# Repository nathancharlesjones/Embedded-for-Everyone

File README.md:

# Embedded for Everyone
A collection of resources for the hobbyists, students, teachers, and makers who want to develop professional-grade embedded systems but who lack the resources of a commercial enterprise.

See the [wiki for this repository](https://github.com/nathancharlesjones/Embedded-for-Everyone/wiki) for additional information and an explanation of the files contained herein.

## File structure
```
./
├── Getting-Started-Guides
│   ├── LPC845-BRK
│   │   ├── Command-line
│   │   │   ├── Blinky_v2
│   │   │   ├── Blinky_v3
│   │   │   ├── OpenOCD_and_CMSIS-DAP.sh
│   │   │   └── OpenOCD_and_J-Link.sh
│   │   ├── NXP-MCUXpresso
│   │   ├── Segger-Embedded-Studio
│   │   └── Getting-Started-with-the-LPC845-BRK.pdf
│   ├── MSP430
│   │   ├── CCStudio
│   │   ├── Getting-Started-with-the-MSP430.pdf
│   │   └── MSP430G2553.fzz
│   ├── PIC16-PIC18-dsPIC33
│   │   ├── dsPIC33
│   │   │   ├── Command-line
│   │   │   └── MPLAB-X
│   │   ├── PIC16
│   │   │   ├── Command-line
│   │   │   └── MPLAB-X
│   │   ├── dsPIC33EV32GM002.fzz
│   │   ├── Getting-Started-with-the-PIC16-PIC18-dsPIC33.pdf
│   │   └── PIC16F18446.fzz
│   ├── STM32G031J6
│   │   ├── Command-line
│   │   │   ├── libopencm3
│   │   │   ├── STM32Cube
│   │   │   ├── Start-ST-Link-GDB-Server.sh
│   │   │   └── Start-ST-Link-GDB-Server_v2.sh
│   │   ├── Keil-MDK-Arm
│   │   ├── STM32CubeIDE
│   │   └── Getting-Started-with-the-STM32G031J6.pdf
│   ├── XMC2GO_XMC1100
│   │   ├── Command-line
│   │   │   ├── Blinky
│   │   │   ├── Blinky_v2
│   │   │   └── OpenOCD_and_J-Link.sh
│   │   ├── DAVE
│   │   ├── Segger-Embedded-Studio
│   │   ├── VS-Code
│   │   └── Getting-Started-with-the-XMC2GO-XMC1100.pdf
│   ├── Compatible-Toolchains.csv
│   └── Compatible-Toolchains.ods
├── Printed-Circuit-Boards
│   ├── Breakout-boards
│   │   ├── STM32F030F4P6-Breakout-Boards
│   │   └── STM32G0-Breakout-Boards
│   ├── Eagle-Design-Rule-Files
│   └── Prototyping-PCBs
│       ├── Breadboard-Panelized
│       ├── Breadboard-Single
│       ├── Stripboard-Panelized
│       ├── Stripboard-Single
│       └── README.md
├── Supporting-documents
├── Embedded-for-Everyone.pdf
├── LICENSE
└── README.md
```

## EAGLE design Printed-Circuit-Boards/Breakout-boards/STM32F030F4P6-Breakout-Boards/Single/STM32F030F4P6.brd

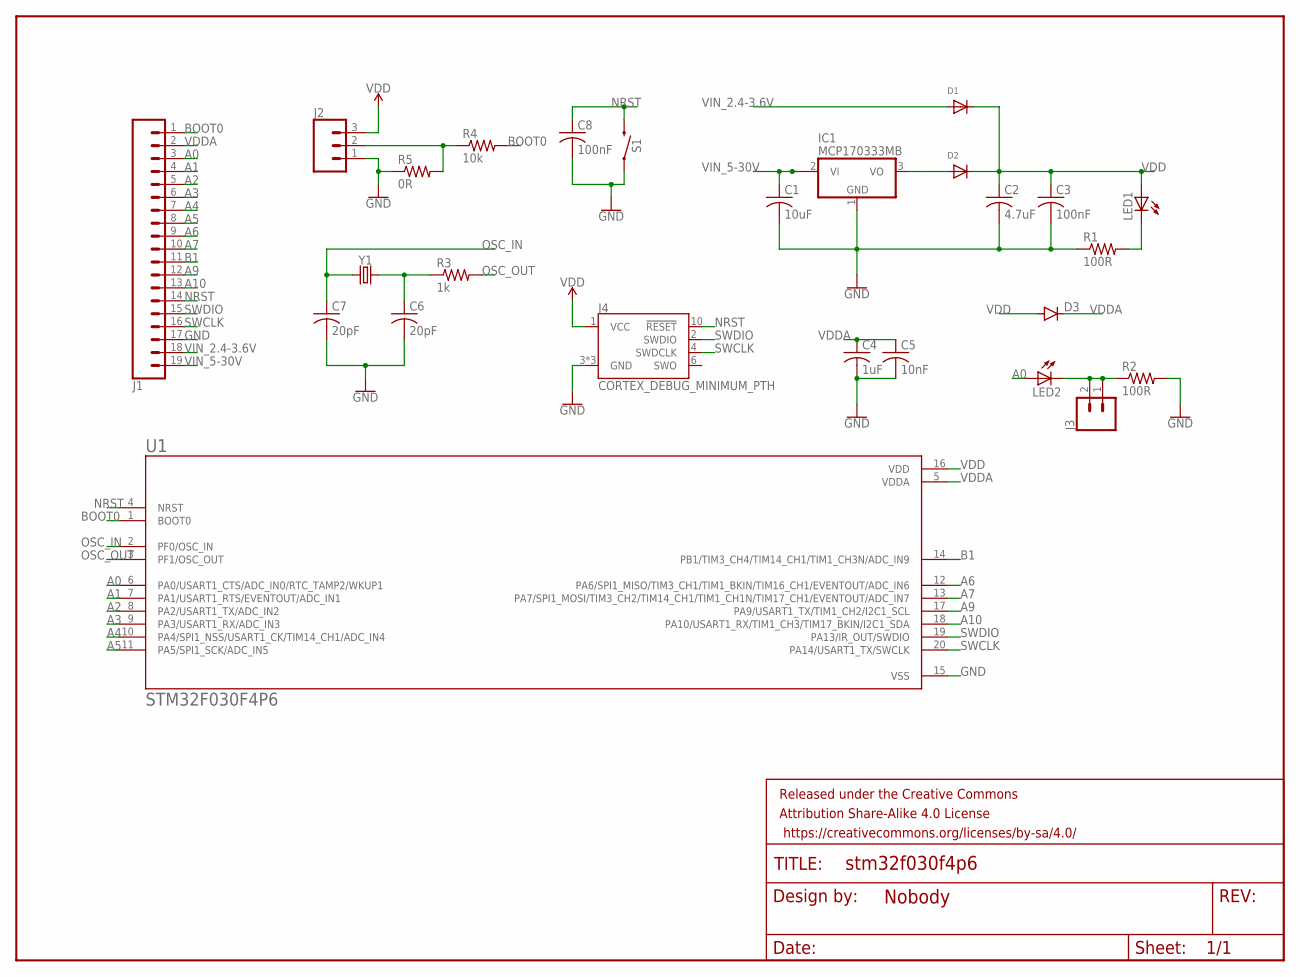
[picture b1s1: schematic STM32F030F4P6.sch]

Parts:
C1: 10uF; C0603
C2: 4.7uF; C0603
C3, C8: 100nF; C0603
C4: 1uF; C0603
C5: 10nF; C0603
C6, C7: 20pF; C0603
D1, D2: DIODESOD-123; SOD-123
D3: DIODE-DO-214AC; DO-214AC
FRAME2: FRAME-LETTERNO_PACKAGE; DUMMY
IC1: MCP170333MB; SOT89
J1: CONN_19; 1X19
J2: 455-1750-1-ND; 1X03
J3: CONN_02; 1X02
J4: CORTEX_DEBUG_MINIMUM_PTH; 2X5-PTH-1.27MM
LED1, LED2: LEDCHIPLED_0603; CHIPLED_0603
R1, R2: 100R; R0603
R3: 1k; R0603
R4: 10k; R0603
R5: 0R; R0603
S1: MOMENTARY-SWITCH-SPST-SMD-5.2-REDUNDANT; TACTILE_SWITCH_SMD_5.2MM
U1: STM32F030F4P6; SOP65P640X120-20N
Y1: CRYSTALSMD-5X3.2-2PAD; CRYSTAL-SMD-5X3.2-2PAD

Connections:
A0: J1.3, LED2.A, U1.6 (PA0/USART1_CTS/ADC_IN0/RTC_TAMP2/WKUP1)
A1: J1.4, U1.7 (PA1/USART1_RTS/EVENTOUT/ADC_IN1)
A2: J1.5, U1.8 (PA2/USART1_TX/ADC_IN2)
A3: J1.6, U1.9 (PA3/USART1_RX/ADC_IN3)
A4: J1.7, U1.10 (PA4/SPI1_NSS/USART1_CK/TIM14_CH1/ADC_IN4)
A5: J1.8, U1.11 (PA5/SPI1_SCK/ADC_IN5)
A6: J1.9, U1.12 (PA6/SPI1_MISO/TIM3_CH1/TIM1_BKIN/TIM16_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)
A7: J1.10, U1.13 (PA7/SPI1_MOSI/TIM3_CH2/TIM14_CH1/TIM1_C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)
A9: J1.12, U1.17 (PA9/USART1_TX/TIM1_CH2/I2C1_SCL)
A10: J1.13, U1.18 (PA10/USART1_RX/TIM1_CH3/TIM17_BKIN/I2C1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)
B1: J1.11, U1.14 (PB1/TIM3_CH4/TIM14_CH1/TIM1_CH3N/ADC_IN9)
BOOT0: J1.1, R4.2, U1.1 (BOOT0)
GND: C1.2, C2.2, C3.2, C4.2, C5.2, C6.2, C7.2, C8.2, IC1.1 (GND), J1.17, J2.1, J4.3 (GND), J4.5 (GND), J4.9 (GND), R1.1, R2.2, R5.1, S1.1, S1.2 (1), U1.15 (VSS)
unnamed: J2.2, R4.1, R5.2
unnamed: J3.1, J3.2, LED2.C, R2.1
unnamed: C6.1, R3.1, Y1.P$1 (1)
unnamed: D2.A, IC1.3 (VO)
unnamed: LED1.C, R1.2
NRST: C8.1, J1.14, J4.10 (!RESET), S1.3 (2), S1.4 (2), U1.4 (NRST)
OSC_IN: C7.1, U1.2 (PF0/OSC_IN), Y1.P$2 (2)
OSC_OUT: R3.2, U1.3 (PF1/OSC_OUT)
SWCLK: J1.16, J4.4 (SWDCLK), U1.20 (PA14/USART1_TX/SWCLK)
SWDIO: J1.15, J4.2 (SWDIO), U1.19 (PA13/IR_OUT/SWDIO)
VDD: C2.1, C3.1, D1.C, D2.C, D3.A, J2.3, J4.1 (VCC), LED1.A, U1.16 (VDD)
VDDA: C4.1, C5.1, D3.C, J1.2, U1.5 (VDDA)
VIN_2.4-3.6V: D1.A, J1.18
VIN_5-30V: C1.1, IC1.2@1 (VI1), J1.19

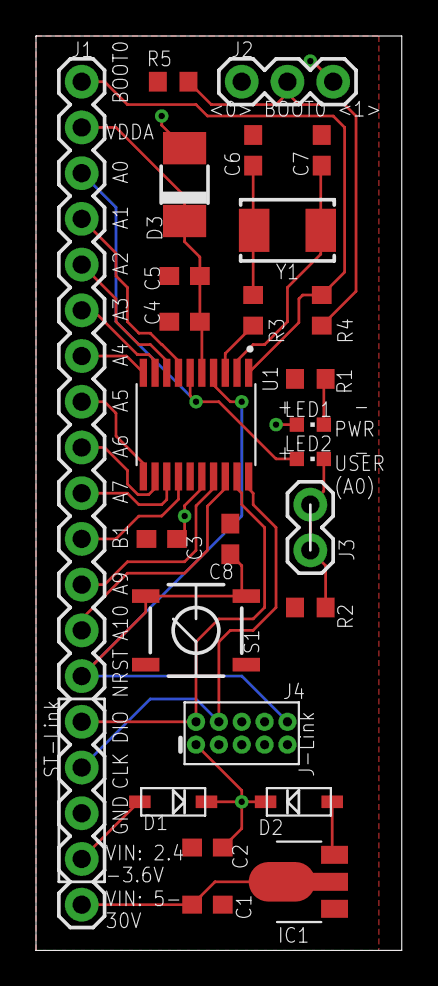
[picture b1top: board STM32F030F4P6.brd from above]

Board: 2 copper layers, 20.3 x 50.8 mm, 27 parts (0 on the bottom side), 27 nets.

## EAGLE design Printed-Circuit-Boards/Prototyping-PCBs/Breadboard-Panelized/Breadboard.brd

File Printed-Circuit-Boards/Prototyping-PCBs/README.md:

For information about the differences between stripboard and breadboard-style protoboard, see [here](https://github.com/nathancharlesjones/Embedded-for-Everyone/wiki/3.-Building-a-circuit-on-a-PCB-and-connecting-it-to-the-rest-of-the-embedded-device#step-3-lay-out-the-pcb-or-get-a-protoboard).

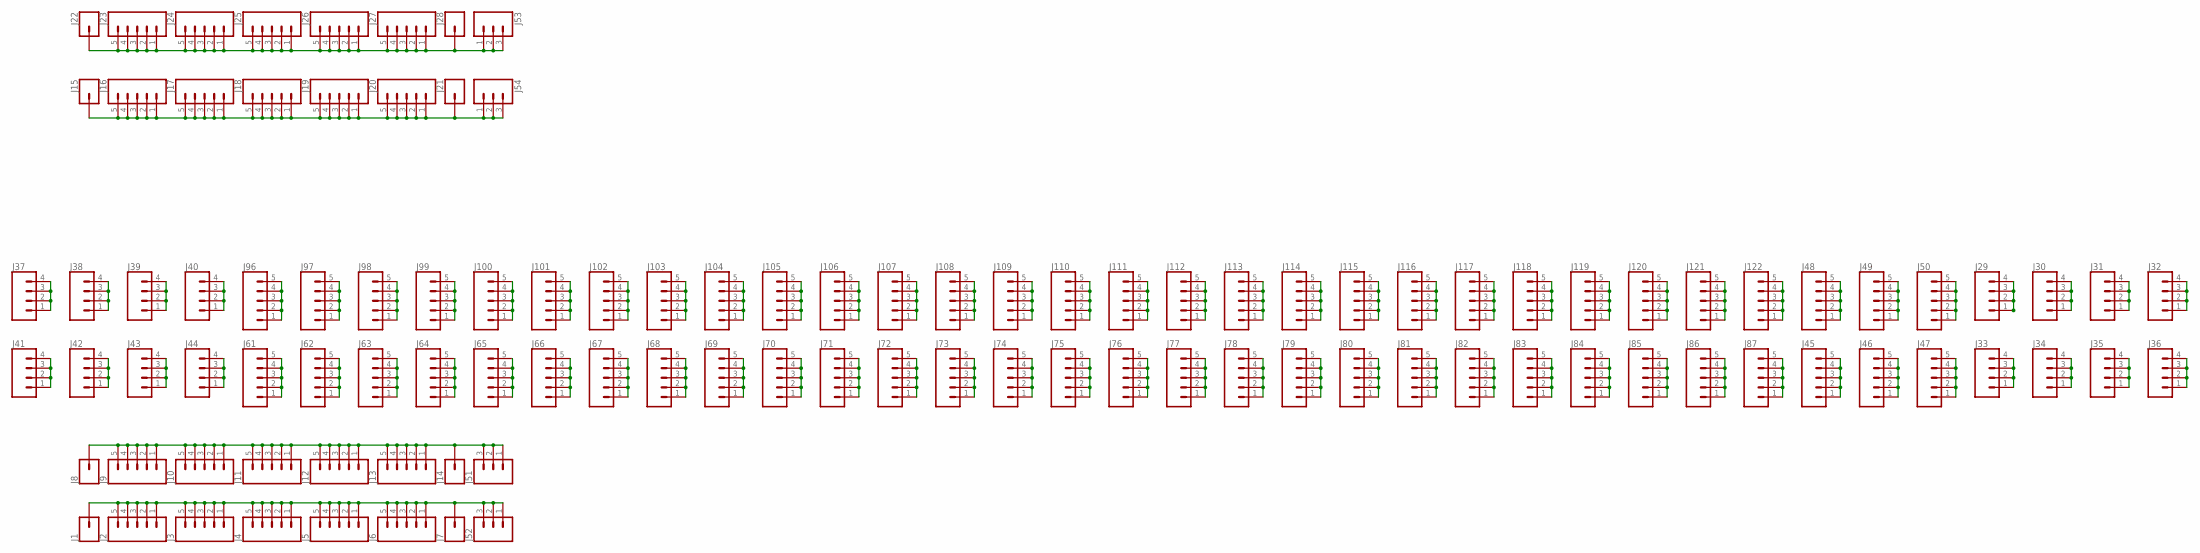
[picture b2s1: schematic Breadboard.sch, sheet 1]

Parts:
J1, J7, J8, J14, J15, J21, J22, J28: CONN_01; 1X01
J2, J3, J4, J5, J6, J9, J10, J11, J12, J13, J16, J17, J18, J19, J20, J23, J24, J25, J26, J27, J45, J46, J47, J48, J49, J50, J61, J62, J63, J64, J65, J66, J67, J68, J69, J70, J71, J72, J73, J74, J75, J76, J77, J78, J79, J80, J81, J82, J83, J84, J85, J86, J87, J96, J97, J98, J99, J100, J101, J102, J103, J104, J105, J106, J107, J108, J109, J110, J111, J112, J113, J114, J115, J116, J117, J118, J119, J120, J121, J122: CONN_05; 1X05
J29, J30, J31, J32, J33, J34, J35, J36, J37, J38, J39, J40, J41, J42, J43, J44: CONN_04PTH; 1X04
J51, J52, J53, J54: 455-1750-1-ND; 1X03

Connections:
unnamed: J1.1, J2.1, J2.2, J2.3, J2.4, J2.5, J3.1, J3.2, J3.3, J3.4, J3.5, J4.1, J4.2, J4.3, J4.4, J4.5, J5.1, J5.2, J5.3, J5.4, J5.5, J6.1, J6.2, J6.3, J6.4, J6.5, J7.1, J52.1, J52.2, J52.3
unnamed: J8.1, J9.1, J9.2, J9.3, J9.4, J9.5, J10.1, J10.2, J10.3, J10.4, J10.5, J11.1, J11.2, J11.3, J11.4, J11.5, J12.1, J12.2, J12.3, J12.4, J12.5, J13.1, J13.2, J13.3, J13.4, J13.5, J14.1, J51.1, J51.2, J51.3
unnamed: J15.1, J16.1, J16.2, J16.3, J16.4, J16.5, J17.1, J17.2, J17.3, J17.4, J17.5, J18.1, J18.2, J18.3, J18.4, J18.5, J19.1, J19.2, J19.3, J19.4, J19.5, J20.1, J20.2, J20.3, J20.4, J20.5, J21.1, J54.1, J54.2, J54.3
unnamed: J22.1, J23.1, J23.2, J23.3, J23.4, J23.5, J24.1, J24.2, J24.3, J24.4, J24.5, J25.1, J25.2, J25.3, J25.4, J25.5, J26.1, J26.2, J26.3, J26.4, J26.5, J27.1, J27.2, J27.3, J27.4, J27.5, J28.1, J53.1, J53.2, J53.3
unnamed: J41.1, J41.2, J41.3, J41.4
unnamed: J42.1, J42.2, J42.3, J42.4
unnamed: J43.1, J43.2, J43.3, J43.4
unnamed: J44.1, J44.2, J44.3, J44.4
unnamed: J61.1, J61.2, J61.3, J61.4, J61.5
unnamed: J62.1, J62.2, J62.3, J62.4, J62.5
unnamed: J63.1, J63.2, J63.3, J63.4, J63.5
unnamed: J64.1, J64.2, J64.3, J64.4, J64.5
unnamed: J65.1, J65.2, J65.3, J65.4, J65.5
unnamed: J66.1, J66.2, J66.3, J66.4, J66.5
unnamed: J67.1, J67.2, J67.3, J67.4, J67.5
unnamed: J68.1, J68.2, J68.3, J68.4, J68.5
unnamed: J69.1, J69.2, J69.3, J69.4, J69.5
unnamed: J70.1, J70.2, J70.3, J70.4, J70.5
unnamed: J71.1, J71.2, J71.3, J71.4, J71.5
unnamed: J72.1, J72.2, J72.3, J72.4, J72.5
unnamed: J73.1, J73.2, J73.3, J73.4, J73.5
unnamed: J74.1, J74.2, J74.3, J74.4, J74.5
unnamed: J75.1, J75.2, J75.3, J75.4, J75.5
unnamed: J76.1, J76.2, J76.3, J76.4, J76.5
unnamed: J77.1, J77.2, J77.3, J77.4, J77.5
unnamed: J78.1, J78.2, J78.3, J78.4, J78.5
unnamed: J79.1, J79.2, J79.3, J79.4, J79.5
unnamed: J80.1, J80.2, J80.3, J80.4, J80.5
unnamed: J81.1, J81.2, J81.3, J81.4, J81.5
unnamed: J82.1, J82.2, J82.3, J82.4, J82.5
unnamed: J83.1, J83.2, J83.3, J83.4, J83.5
unnamed: J84.1, J84.2, J84.3, J84.4, J84.5
unnamed: J85.1, J85.2, J85.3, J85.4, J85.5
unnamed: J86.1, J86.2, J86.3, J86.4, J86.5
unnamed: J87.1, J87.2, J87.3, J87.4, J87.5
unnamed: J33.1, J33.2, J33.3, J33.4
unnamed: J34.1, J34.2, J34.3, J34.4
unnamed: J35.1, J35.2, J35.3, J35.4
unnamed: J36.1, J36.2, J36.3, J36.4
unnamed: J37.1, J37.2, J37.3, J37.4
unnamed: J38.1, J38.2, J38.3, J38.4
unnamed: J39.1, J39.2, J39.3, J39.4
unnamed: J40.1, J40.2, J40.3, J40.4
unnamed: J96.1, J96.2, J96.3, J96.4, J96.5
unnamed: J97.1, J97.2, J97.3, J97.4, J97.5
unnamed: J98.1, J98.2, J98.3, J98.4, J98.5
unnamed: J99.1, J99.2, J99.3, J99.4, J99.5
unnamed: J100.1, J100.2, J100.3, J100.4, J100.5
unnamed: J101.1, J101.2, J101.3, J101.4, J101.5
unnamed: J102.1, J102.2, J102.3, J102.4, J102.5
unnamed: J103.1, J103.2, J103.3, J103.4, J103.5
unnamed: J104.1, J104.2, J104.3, J104.4, J104.5
unnamed: J105.1, J105.2, J105.3, J105.4, J105.5
unnamed: J106.1, J106.2, J106.3, J106.4, J106.5
unnamed: J107.1, J107.2, J107.3, J107.4, J107.5
unnamed: J108.1, J108.2, J108.3, J108.4, J108.5
unnamed: J109.1, J109.2, J109.3, J109.4, J109.5
unnamed: J110.1, J110.2, J110.3, J110.4, J110.5
unnamed: J111.1, J111.2, J111.3, J111.4, J111.5
unnamed: J112.1, J112.2, J112.3, J112.4, J112.5
unnamed: J113.1, J113.2, J113.3, J113.4, J113.5
unnamed: J114.1, J114.2, J114.3, J114.4, J114.5
unnamed: J115.1, J115.2, J115.3, J115.4, J115.5
unnamed: J116.1, J116.2, J116.3, J116.4, J116.5
unnamed: J117.1, J117.2, J117.3, J117.4, J117.5
unnamed: J118.1, J118.2, J118.3, J118.4, J118.5
unnamed: J119.1, J119.2, J119.3, J119.4, J119.5
unnamed: J120.1, J120.2, J120.3, J120.4, J120.5
unnamed: J121.1, J121.2, J121.3, J121.4, J121.5
unnamed: J122.1, J122.2, J122.3, J122.4, J122.5
unnamed: J29.1, J29.2, J29.3, J29.4
unnamed: J30.1, J30.2, J30.3, J30.4
unnamed: J31.1, J31.2, J31.3, J31.4
unnamed: J32.1, J32.2, J32.3, J32.4
unnamed: J48.1, J48.2, J48.3, J48.4, J48.5
unnamed: J45.1, J45.2, J45.3, J45.4, J45.5
unnamed: J46.1, J46.2, J46.3, J46.4, J46.5
unnamed: J47.1, J47.2, J47.3, J47.4, J47.5
unnamed: J49.1, J49.2, J49.3, J49.4, J49.5
unnamed: J50.1, J50.2, J50.3, J50.4, J50.5

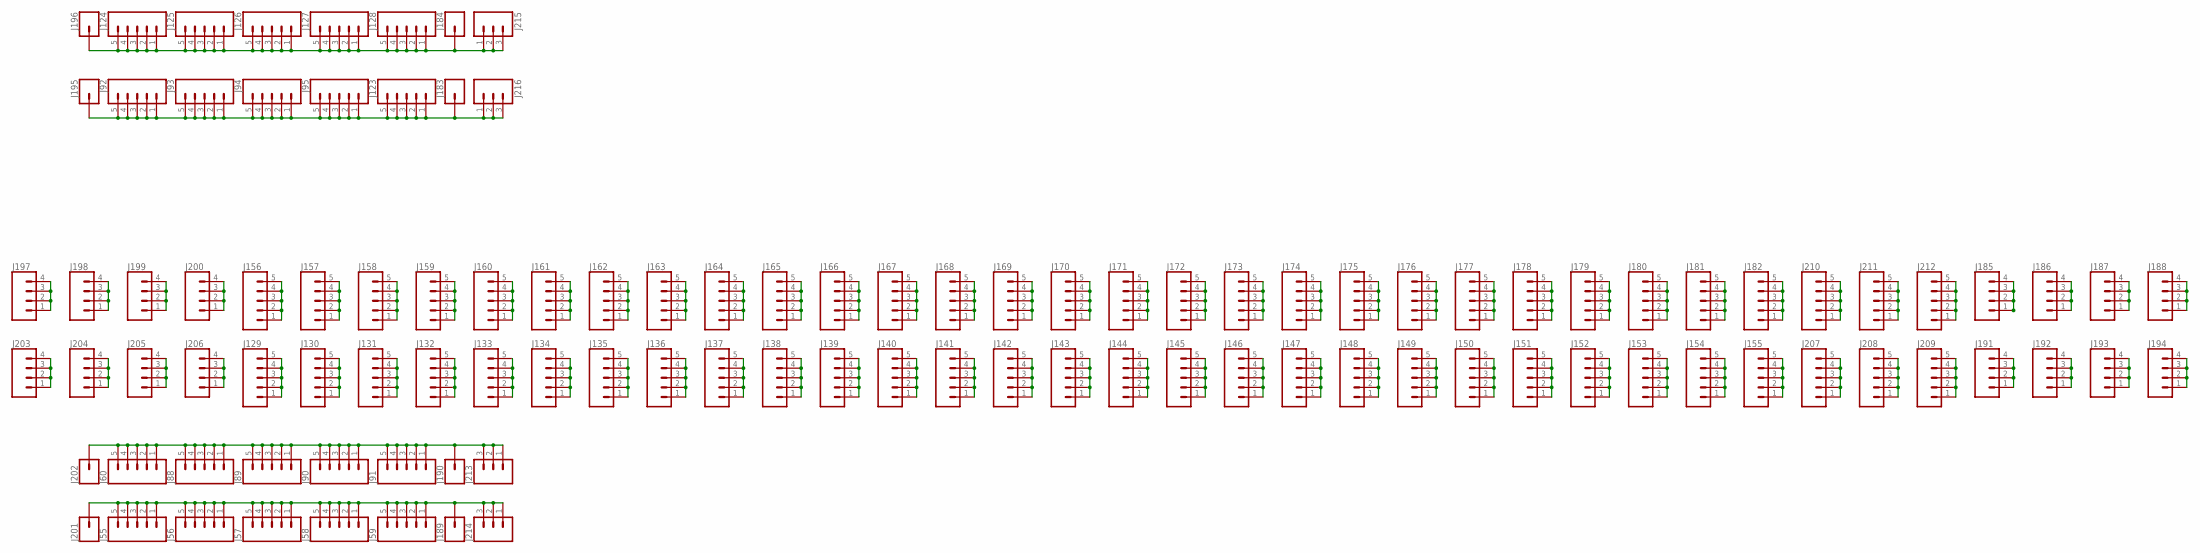
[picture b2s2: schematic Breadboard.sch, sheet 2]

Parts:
J55, J56, J57, J58, J59, J60, J88, J89, J90, J91, J92, J93, J94, J95, J123, J124, J125, J126, J127, J128, J129, J130, J131, J132, J133, J134, J135, J136, J137, J138, J139, J140, J141, J142, J143, J144, J145, J146, J147, J148, J149, J150, J151, J152, J153, J154, J155, J156, J157, J158, J159, J160, J161, J162, J163, J164, J165, J166, J167, J168, J169, J170, J171, J172, J173, J174, J175, J176, J177, J178, J179, J180, J181, J182, J207, J208, J209, J210, J211, J212: CONN_05; 1X05
J183, J184, J189, J190, J195, J196, J201, J202: CONN_01; 1X01
J185, J186, J187, J188, J191, J192, J193, J194, J197, J198, J199, J200, J203, J204, J205, J206: CONN_04PTH; 1X04
J213, J214, J215, J216: 455-1750-1-ND; 1X03

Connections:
unnamed: J55.1, J55.2, J55.3, J55.4, J55.5, J56.1, J56.2, J56.3, J56.4, J56.5, J57.1, J57.2, J57.3, J57.4, J57.5, J58.1, J58.2, J58.3, J58.4, J58.5, J59.1, J59.2, J59.3, J59.4, J59.5, J189.1, J201.1, J214.1, J214.2, J214.3
unnamed: J60.1, J60.2, J60.3, J60.4, J60.5, J88.1, J88.2, J88.3, J88.4, J88.5, J89.1, J89.2, J89.3, J89.4, J89.5, J90.1, J90.2, J90.3, J90.4, J90.5, J91.1, J91.2, J91.3, J91.4, J91.5, J190.1, J202.1, J213.1, J213.2, J213.3
unnamed: J92.1, J92.2, J92.3, J92.4, J92.5, J93.1, J93.2, J93.3, J93.4, J93.5, J94.1, J94.2, J94.3, J94.4, J94.5, J95.1, J95.2, J95.3, J95.4, J95.5, J123.1, J123.2, J123.3, J123.4, J123.5, J183.1, J195.1, J216.1, J216.2, J216.3
unnamed: J124.1, J124.2, J124.3, J124.4, J124.5, J125.1, J125.2, J125.3, J125.4, J125.5, J126.1, J126.2, J126.3, J126.4, J126.5, J127.1, J127.2, J127.3, J127.4, J127.5, J128.1, J128.2, J128.3, J128.4, J128.5, J184.1, J196.1, J215.1, J215.2, J215.3
unnamed: J203.1, J203.2, J203.3, J203.4
unnamed: J204.1, J204.2, J204.3, J204.4
unnamed: J205.1, J205.2, J205.3, J205.4
unnamed: J206.1, J206.2, J206.3, J206.4
unnamed: J129.1, J129.2, J129.3, J129.4, J129.5
unnamed: J130.1, J130.2, J130.3, J130.4, J130.5
unnamed: J131.1, J131.2, J131.3, J131.4, J131.5
unnamed: J132.1, J132.2, J132.3, J132.4, J132.5
unnamed: J133.1, J133.2, J133.3, J133.4, J133.5
unnamed: J134.1, J134.2, J134.3, J134.4, J134.5
unnamed: J135.1, J135.2, J135.3, J135.4, J135.5
unnamed: J136.1, J136.2, J136.3, J136.4, J136.5
unnamed: J137.1, J137.2, J137.3, J137.4, J137.5
unnamed: J138.1, J138.2, J138.3, J138.4, J138.5
unnamed: J139.1, J139.2, J139.3, J139.4, J139.5
unnamed: J140.1, J140.2, J140.3, J140.4, J140.5
unnamed: J141.1, J141.2, J141.3, J141.4, J141.5
unnamed: J142.1, J142.2, J142.3, J142.4, J142.5
unnamed: J143.1, J143.2, J143.3, J143.4, J143.5
unnamed: J144.1, J144.2, J144.3, J144.4, J144.5
unnamed: J145.1, J145.2, J145.3, J145.4, J145.5
unnamed: J146.1, J146.2, J146.3, J146.4, J146.5
unnamed: J147.1, J147.2, J147.3, J147.4, J147.5
unnamed: J148.1, J148.2, J148.3, J148.4, J148.5
unnamed: J149.1, J149.2, J149.3, J149.4, J149.5
unnamed: J150.1, J150.2, J150.3, J150.4, J150.5
unnamed: J151.1, J151.2, J151.3, J151.4, J151.5
unnamed: J152.1, J152.2, J152.3, J152.4, J152.5
unnamed: J153.1, J153.2, J153.3, J153.4, J153.5
unnamed: J154.1, J154.2, J154.3, J154.4, J154.5
unnamed: J155.1, J155.2, J155.3, J155.4, J155.5
unnamed: J191.1, J191.2, J191.3, J191.4
unnamed: J192.1, J192.2, J192.3, J192.4
unnamed: J193.1, J193.2, J193.3, J193.4
unnamed: J194.1, J194.2, J194.3, J194.4
unnamed: J197.1, J197.2, J197.3, J197.4
unnamed: J198.1, J198.2, J198.3, J198.4
unnamed: J199.1, J199.2, J199.3, J199.4
unnamed: J200.1, J200.2, J200.3, J200.4
unnamed: J156.1, J156.2, J156.3, J156.4, J156.5
unnamed: J157.1, J157.2, J157.3, J157.4, J157.5
unnamed: J158.1, J158.2, J158.3, J158.4, J158.5
unnamed: J159.1, J159.2, J159.3, J159.4, J159.5
unnamed: J160.1, J160.2, J160.3, J160.4, J160.5
unnamed: J161.1, J161.2, J161.3, J161.4, J161.5
unnamed: J162.1, J162.2, J162.3, J162.4, J162.5
unnamed: J163.1, J163.2, J163.3, J163.4, J163.5
unnamed: J164.1, J164.2, J164.3, J164.4, J164.5
unnamed: J165.1, J165.2, J165.3, J165.4, J165.5
unnamed: J166.1, J166.2, J166.3, J166.4, J166.5
unnamed: J167.1, J167.2, J167.3, J167.4, J167.5
unnamed: J168.1, J168.2, J168.3, J168.4, J168.5
unnamed: J169.1, J169.2, J169.3, J169.4, J169.5
unnamed: J170.1, J170.2, J170.3, J170.4, J170.5
unnamed: J171.1, J171.2, J171.3, J171.4, J171.5
unnamed: J172.1, J172.2, J172.3, J172.4, J172.5
unnamed: J173.1, J173.2, J173.3, J173.4, J173.5
unnamed: J174.1, J174.2, J174.3, J174.4, J174.5
unnamed: J175.1, J175.2, J175.3, J175.4, J175.5
unnamed: J176.1, J176.2, J176.3, J176.4, J176.5
unnamed: J177.1, J177.2, J177.3, J177.4, J177.5
unnamed: J178.1, J178.2, J178.3, J178.4, J178.5
unnamed: J179.1, J179.2, J179.3, J179.4, J179.5
unnamed: J180.1, J180.2, J180.3, J180.4, J180.5
unnamed: J181.1, J181.2, J181.3, J181.4, J181.5
unnamed: J182.1, J182.2, J182.3, J182.4, J182.5
unnamed: J185.1, J185.2, J185.3, J185.4
unnamed: J186.1, J186.2, J186.3, J186.4
unnamed: J187.1, J187.2, J187.3, J187.4
unnamed: J188.1, J188.2, J188.3, J188.4
unnamed: J207.1, J207.2, J207.3, J207.4, J207.5
unnamed: J208.1, J208.2, J208.3, J208.4, J208.5
unnamed: J209.1, J209.2, J209.3, J209.4, J209.5
unnamed: J210.1, J210.2, J210.3, J210.4, J210.5
unnamed: J211.1, J211.2, J211.3, J211.4, J211.5
unnamed: J212.1, J212.2, J212.3, J212.4, J212.5

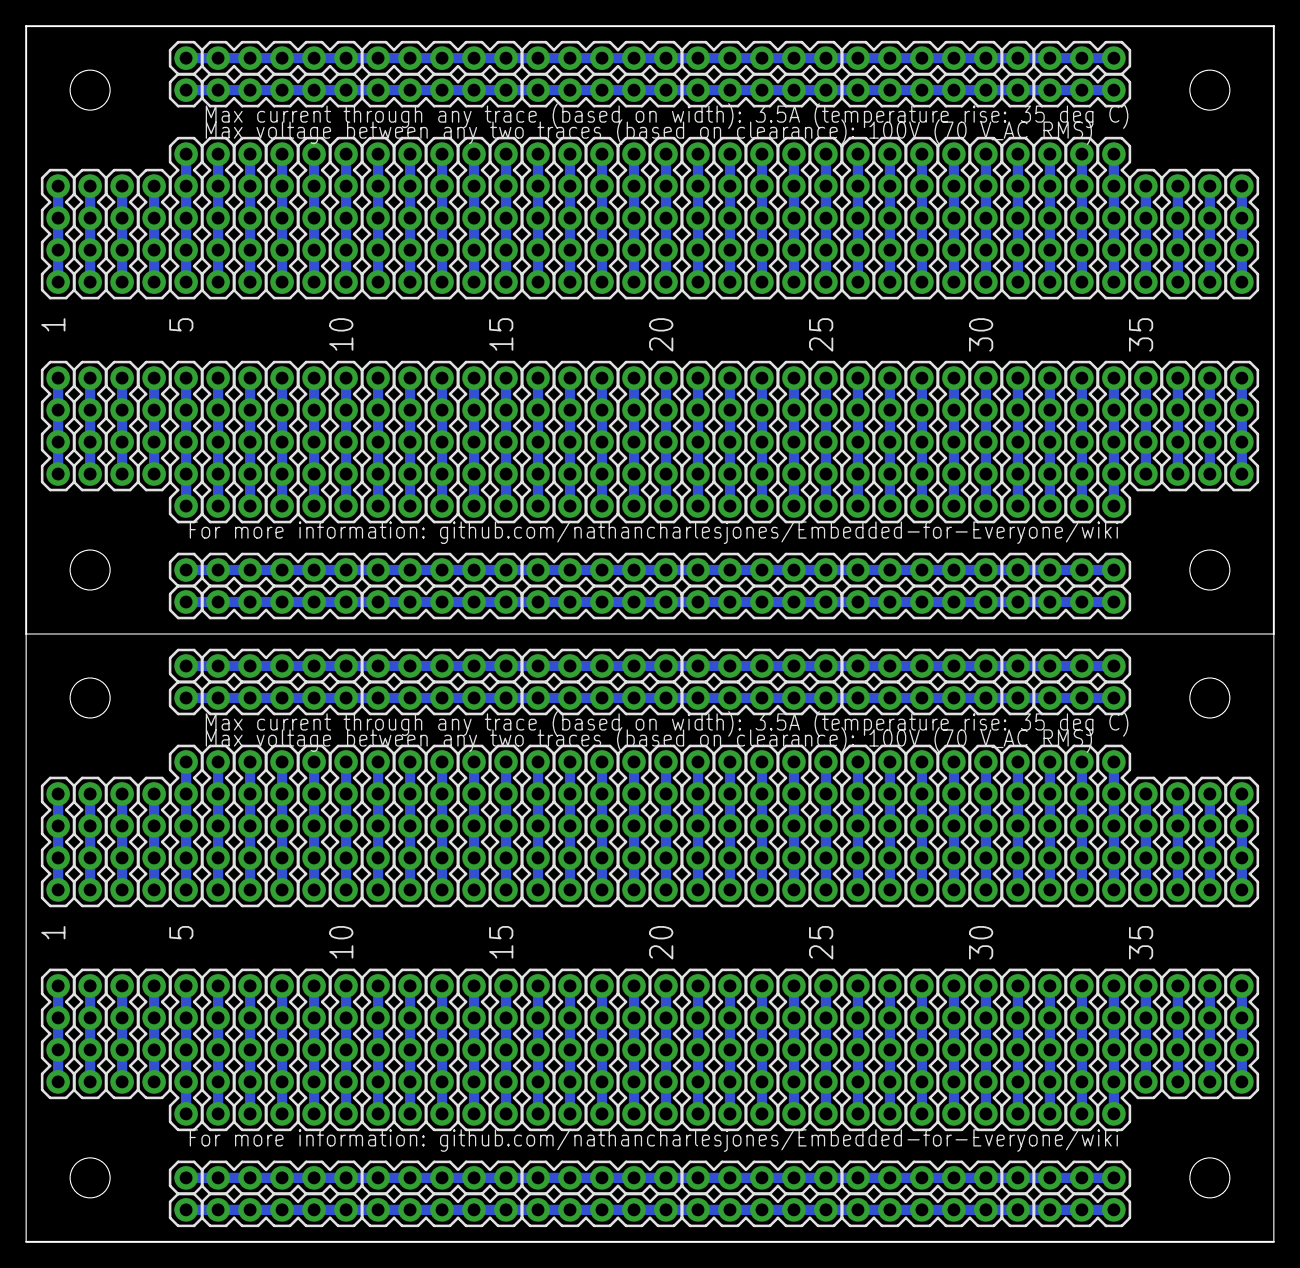
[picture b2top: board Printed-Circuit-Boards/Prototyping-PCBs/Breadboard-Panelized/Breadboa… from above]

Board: 2 copper layers, 99.1 x 96.5 mm, 216 parts (0 on the bottom side), 160 nets.

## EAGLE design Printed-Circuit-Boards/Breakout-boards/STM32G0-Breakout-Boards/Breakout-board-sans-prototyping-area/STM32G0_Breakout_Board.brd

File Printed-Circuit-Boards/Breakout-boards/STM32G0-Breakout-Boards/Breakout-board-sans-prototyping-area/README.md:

For information about how to order this PCB (either unassembled for full assembled), see [here](https://github.com/nathancharlesjones/Embedded-for-Everyone/wiki/3.-Building-a-circuit-on-a-PCB-and-connecting-it-to-the-rest-of-the-embedded-device#step-5-assemble-the-pcb).

This board was also designed with large-enough dimensions to be manufactured by hand using a PCB mill or other manual technique. If the method you use doesn't through-plate the vias, don't forget to connect them each yourself.

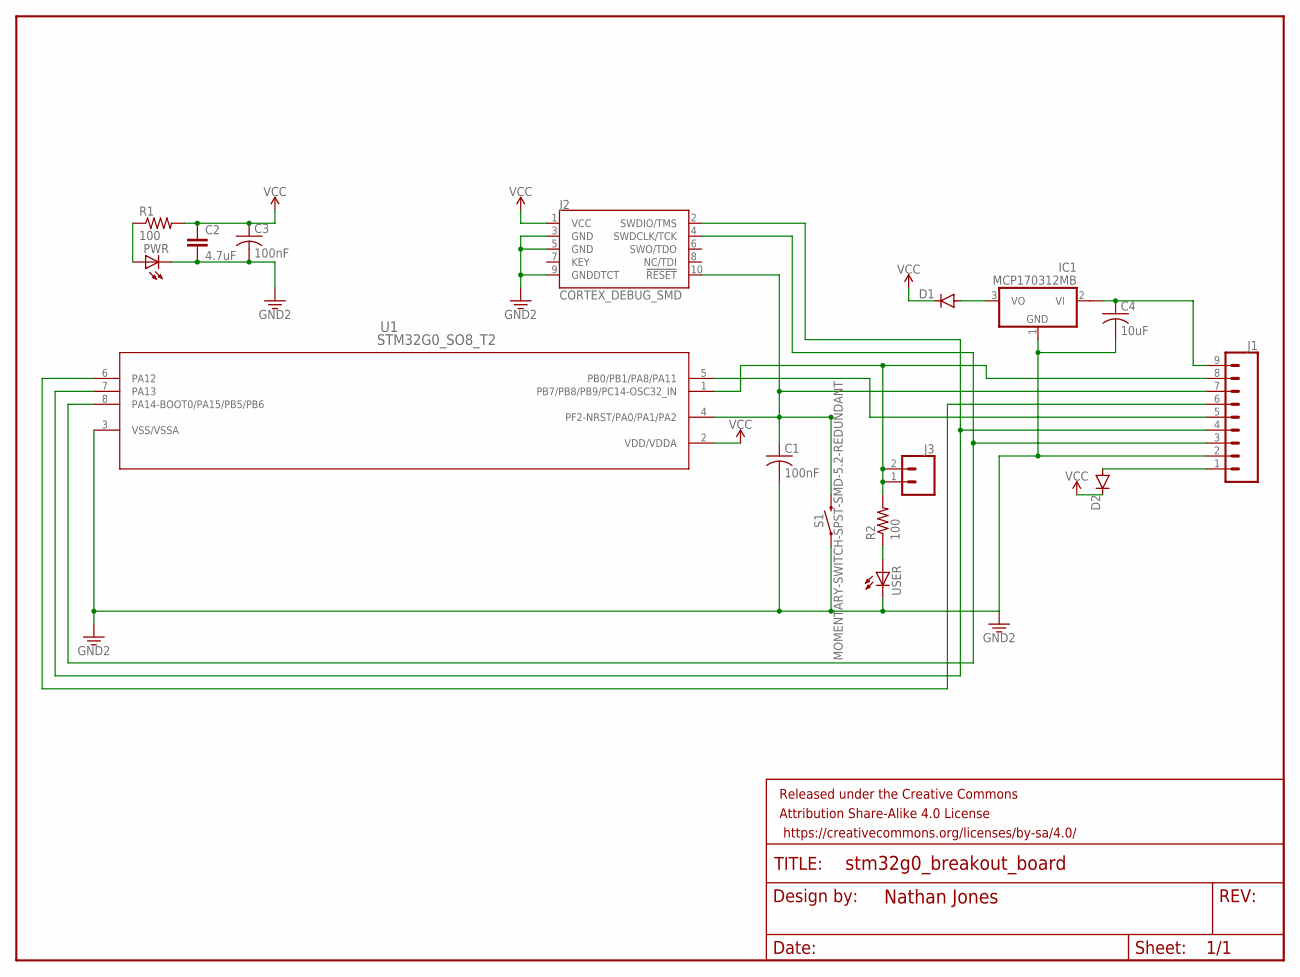
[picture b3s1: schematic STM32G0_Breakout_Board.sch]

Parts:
C1, C3: 100nF; C1206
C2: 4.7uF; 1206
C4: 10uF; C1206
D1, D2: DIODE-DO-214AC; DO-214AC
FRAME1: FRAME-LETTERNO_PACKAGE; DUMMY
IC1: MCP170312MB; SOT89
J1: CONN_09LONGPADS; 1X09_LONGPADS
J2: CORTEX_DEBUG_SMD; SAMTECH_FTSH-105-01
J3: CONN_02PTH3; 1X02_LONGPADS
PWR: LEDCHIP-LED0805; CHIP-LED0805
R1, R2: 100; R1206
S1: MOMENTARY-SWITCH-SPST-SMD-5.2-REDUNDANT; TACTILE_SWITCH_SMD_5.2MM
U1: STM32G0_SO8_T2; SO-8
USER: LEDCHIP-LED0805; CHIP-LED0805

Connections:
GND: C1.2, C2.2, C3.2, C4.2, IC1.1 (GND), J1.2, J2.3 (GND), J2.5 (GND), J2.9 (GNDDTCT), PWR.C, S1.1, S1.2 (1), U1.3 (VSS/VSSA), USER.C
unnamed: R2.1, USER.A
unnamed: D2.A, J1.1
unnamed: C4.1, IC1.2@1 (VI1), J1.9
unnamed: PWR.A, R1.1
unnamed: D1.A, IC1.3 (VO)
NRST/PA0/PA1/PA2: C1.1, J1.7, J2.10 (!RESET), S1.3 (2), S1.4 (2), U1.4 (PF2-NRST/PA0/PA1/PA2)
PA12: J1.6, U1.6 (PA12)
PB0/PB1/PA8/PA11: J1.5, U1.5 (PB0/PB1/PA8/PA11)
PC14: J1.8, J3.1, J3.2, R2.2, U1.1 (PB7/PB8/PB9/PC14-OSC32_IN)
SWDCLK: J1.3, J2.4 (SWDCLK/TCK), U1.8 (PA14-BOOT0/PA15/PB5/PB6)
SWDIO: J1.4, J2.2 (SWDIO/TMS), U1.7 (PA13)
VCC: C2.1, C3.1, D1.C, D2.C, J2.1 (VCC), R1.2, U1.2 (VDD/VDDA)

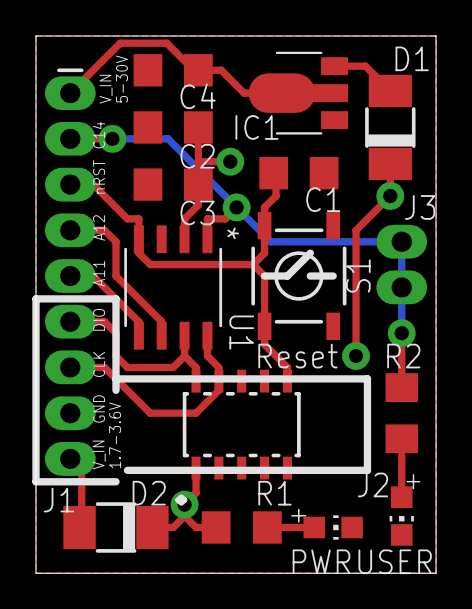
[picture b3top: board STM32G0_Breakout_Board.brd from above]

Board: 2 copper layers, 22.2 x 29.8 mm, 17 parts (0 on the bottom side), 13 nets.

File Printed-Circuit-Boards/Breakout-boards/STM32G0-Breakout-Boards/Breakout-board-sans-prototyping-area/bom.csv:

Comment,Designator,Footprint,LCSC Part #（optional）
100nF,"C1,C3",1206_C,C24497
4.7uF,C2,1206_C,C29823
10uF,C4,1206_C,C13585
,"D1,D2",DO-214AC,C2480
3.3V,IC1,SOT-89-3,C14289
,"PWR,USER",0805,C84256
100Ω,"R1, R2",1206_R,C17901
,S1,5.1mmx5.1mm,C318884
,U1,SOIC-8,C432201

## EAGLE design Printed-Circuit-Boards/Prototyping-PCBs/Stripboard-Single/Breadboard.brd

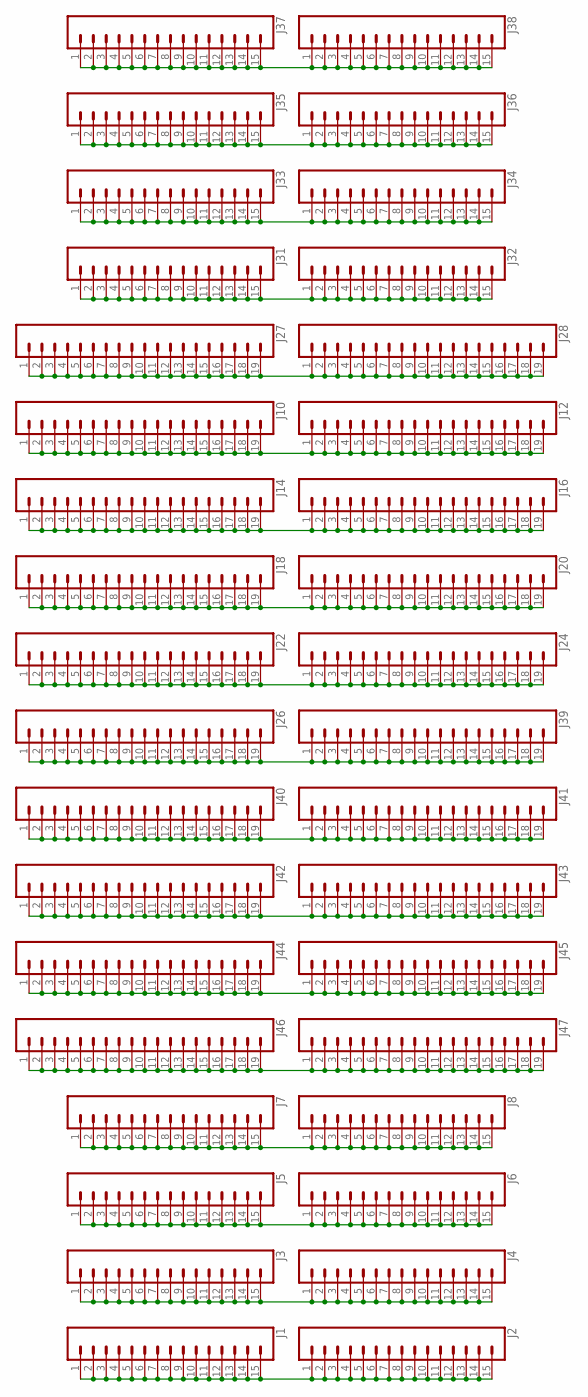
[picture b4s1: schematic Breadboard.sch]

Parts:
J1, J2, J3, J4, J5, J6, J7, J8, J31, J32, J33, J34, J35, J36, J37, J38: CONN_15; 1X15
J10, J12, J14, J16, J18, J20, J22, J24, J26, J27, J28, J39, J40, J41, J42, J43, J44, J45, J46, J47: CONN_19; 1X19

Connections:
unnamed: J37.1, J37.2, J37.3, J37.4, J37.5, J37.6, J37.7, J37.8, J37.9, J37.10, J37.11, J37.12, J37.13, J37.14, J37.15, J38.1, J38.2, J38.3, J38.4, J38.5, J38.6, J38.7, J38.8, J38.9, J38.10, J38.11, J38.12, J38.13, J38.14, J38.15
unnamed: J35.1, J35.2, J35.3, J35.4, J35.5, J35.6, J35.7, J35.8, J35.9, J35.10, J35.11, J35.12, J35.13, J35.14, J35.15, J36.1, J36.2, J36.3, J36.4, J36.5, J36.6, J36.7, J36.8, J36.9, J36.10, J36.11, J36.12, J36.13, J36.14, J36.15
unnamed: J33.1, J33.2, J33.3, J33.4, J33.5, J33.6, J33.7, J33.8, J33.9, J33.10, J33.11, J33.12, J33.13, J33.14, J33.15, J34.1, J34.2, J34.3, J34.4, J34.5, J34.6, J34.7, J34.8, J34.9, J34.10, J34.11, J34.12, J34.13, J34.14, J34.15
unnamed: J31.1, J31.2, J31.3, J31.4, J31.5, J31.6, J31.7, J31.8, J31.9, J31.10, J31.11, J31.12, J31.13, J31.14, J31.15, J32.1, J32.2, J32.3, J32.4, J32.5, J32.6, J32.7, J32.8, J32.9, J32.10, J32.11, J32.12, J32.13, J32.14, J32.15
unnamed: J27.1, J27.2, J27.3, J27.4, J27.5, J27.6, J27.7, J27.8, J27.9, J27.10, J27.11, J27.12, J27.13, J27.14, J27.15, J27.16, J27.17, J27.18, J27.19, J28.1, J28.2, J28.3, J28.4, J28.5, J28.6, J28.7, J28.8, J28.9, J28.10, J28.11, J28.12, J28.13, J28.14, J28.15, J28.16, J28.17, J28.18, J28.19
unnamed: J10.1, J10.2, J10.3, J10.4, J10.5, J10.6, J10.7, J10.8, J10.9, J10.10, J10.11, J10.12, J10.13, J10.14, J10.15, J10.16, J10.17, J10.18, J10.19, J12.1, J12.2, J12.3, J12.4, J12.5, J12.6, J12.7, J12.8, J12.9, J12.10, J12.11, J12.12, J12.13, J12.14, J12.15, J12.16, J12.17, J12.18, J12.19
unnamed: J14.1, J14.2, J14.3, J14.4, J14.5, J14.6, J14.7, J14.8, J14.9, J14.10, J14.11, J14.12, J14.13, J14.14, J14.15, J14.16, J14.17, J14.18, J14.19, J16.1, J16.2, J16.3, J16.4, J16.5, J16.6, J16.7, J16.8, J16.9, J16.10, J16.11, J16.12, J16.13, J16.14, J16.15, J16.16, J16.17, J16.18, J16.19
unnamed: J18.1, J18.2, J18.3, J18.4, J18.5, J18.6, J18.7, J18.8, J18.9, J18.10, J18.11, J18.12, J18.13, J18.14, J18.15, J18.16, J18.17, J18.18, J18.19, J20.1, J20.2, J20.3, J20.4, J20.5, J20.6, J20.7, J20.8, J20.9, J20.10, J20.11, J20.12, J20.13, J20.14, J20.15, J20.16, J20.17, J20.18, J20.19
unnamed: J22.1, J22.2, J22.3, J22.4, J22.5, J22.6, J22.7, J22.8, J22.9, J22.10, J22.11, J22.12, J22.13, J22.14, J22.15, J22.16, J22.17, J22.18, J22.19, J24.1, J24.2, J24.3, J24.4, J24.5, J24.6, J24.7, J24.8, J24.9, J24.10, J24.11, J24.12, J24.13, J24.14, J24.15, J24.16, J24.17, J24.18, J24.19
unnamed: J26.1, J26.2, J26.3, J26.4, J26.5, J26.6, J26.7, J26.8, J26.9, J26.10, J26.11, J26.12, J26.13, J26.14, J26.15, J26.16, J26.17, J26.18, J26.19, J39.1, J39.2, J39.3, J39.4, J39.5, J39.6, J39.7, J39.8, J39.9, J39.10, J39.11, J39.12, J39.13, J39.14, J39.15, J39.16, J39.17, J39.18, J39.19
unnamed: J40.1, J40.2, J40.3, J40.4, J40.5, J40.6, J40.7, J40.8, J40.9, J40.10, J40.11, J40.12, J40.13, J40.14, J40.15, J40.16, J40.17, J40.18, J40.19, J41.1, J41.2, J41.3, J41.4, J41.5, J41.6, J41.7, J41.8, J41.9, J41.10, J41.11, J41.12, J41.13, J41.14, J41.15, J41.16, J41.17, J41.18, J41.19
unnamed: J42.1, J42.2, J42.3, J42.4, J42.5, J42.6, J42.7, J42.8, J42.9, J42.10, J42.11, J42.12, J42.13, J42.14, J42.15, J42.16, J42.17, J42.18, J42.19, J43.1, J43.2, J43.3, J43.4, J43.5, J43.6, J43.7, J43.8, J43.9, J43.10, J43.11, J43.12, J43.13, J43.14, J43.15, J43.16, J43.17, J43.18, J43.19
unnamed: J44.1, J44.2, J44.3, J44.4, J44.5, J44.6, J44.7, J44.8, J44.9, J44.10, J44.11, J44.12, J44.13, J44.14, J44.15, J44.16, J44.17, J44.18, J44.19, J45.1, J45.2, J45.3, J45.4, J45.5, J45.6, J45.7, J45.8, J45.9, J45.10, J45.11, J45.12, J45.13, J45.14, J45.15, J45.16, J45.17, J45.18, J45.19
unnamed: J46.1, J46.2, J46.3, J46.4, J46.5, J46.6, J46.7, J46.8, J46.9, J46.10, J46.11, J46.12, J46.13, J46.14, J46.15, J46.16, J46.17, J46.18, J46.19, J47.1, J47.2, J47.3, J47.4, J47.5, J47.6, J47.7, J47.8, J47.9, J47.10, J47.11, J47.12, J47.13, J47.14, J47.15, J47.16, J47.17, J47.18, J47.19
unnamed: J7.1, J7.2, J7.3, J7.4, J7.5, J7.6, J7.7, J7.8, J7.9, J7.10, J7.11, J7.12, J7.13, J7.14, J7.15, J8.1, J8.2, J8.3, J8.4, J8.5, J8.6, J8.7, J8.8, J8.9, J8.10, J8.11, J8.12, J8.13, J8.14, J8.15
unnamed: J5.1, J5.2, J5.3, J5.4, J5.5, J5.6, J5.7, J5.8, J5.9, J5.10, J5.11, J5.12, J5.13, J5.14, J5.15, J6.1, J6.2, J6.3, J6.4, J6.5, J6.6, J6.7, J6.8, J6.9, J6.10, J6.11, J6.12, J6.13, J6.14, J6.15
unnamed: J3.1, J3.2, J3.3, J3.4, J3.5, J3.6, J3.7, J3.8, J3.9, J3.10, J3.11, J3.12, J3.13, J3.14, J3.15, J4.1, J4.2, J4.3, J4.4, J4.5, J4.6, J4.7, J4.8, J4.9, J4.10, J4.11, J4.12, J4.13, J4.14, J4.15
unnamed: J1.1, J1.2, J1.3, J1.4, J1.5, J1.6, J1.7, J1.8, J1.9, J1.10, J1.11, J1.12, J1.13, J1.14, J1.15, J2.1, J2.2, J2.3, J2.4, J2.5, J2.6, J2.7, J2.8, J2.9, J2.10, J2.11, J2.12, J2.13, J2.14, J2.15

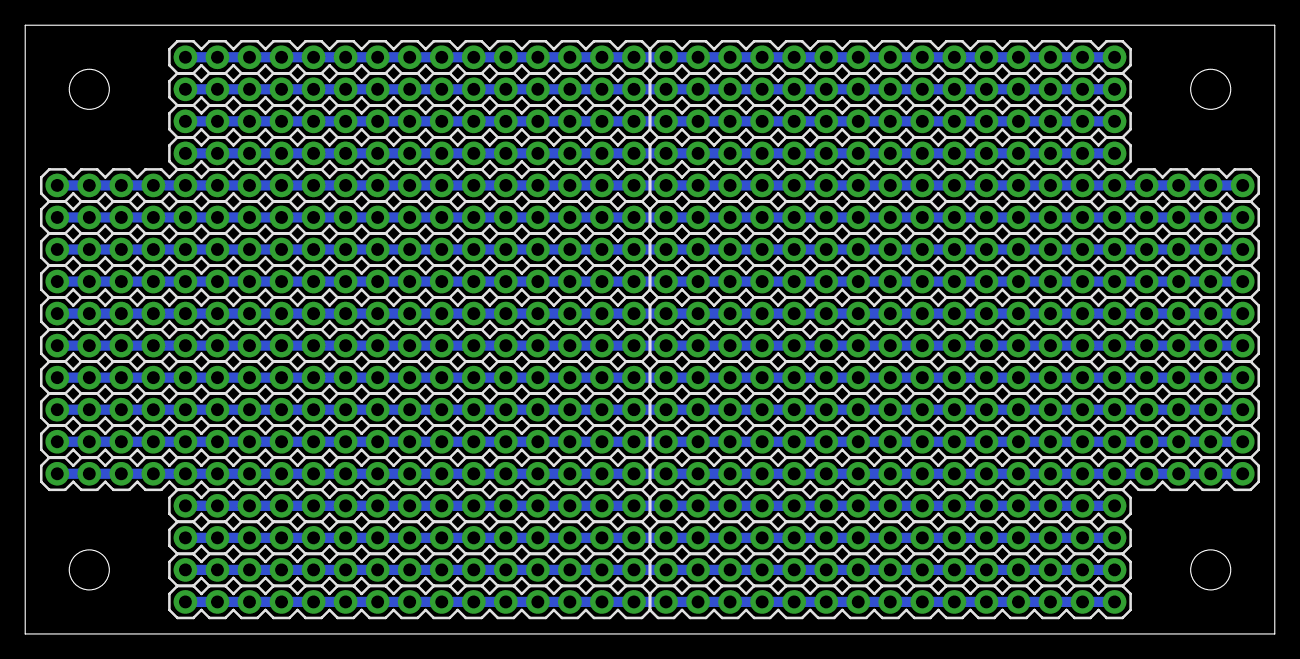
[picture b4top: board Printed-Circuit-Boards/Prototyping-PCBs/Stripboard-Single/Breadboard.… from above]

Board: 2 copper layers, 99.1 x 48.3 mm, 36 parts (0 on the bottom side), 18 nets.

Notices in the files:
parts and their libraries:
SparkFun-Connectors: Licensing: Creative Commons ShareAlike 4.0 International - https://creativecommons.org/licenses/by-sa/4.0
SparkFun-Aesthetics: Released under the Creative Commons Attribution Share-Alike 4.0 License
SparkFun-Aesthetics: https://creativecommons.org/licenses/by-sa/4.0
